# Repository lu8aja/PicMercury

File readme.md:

# PicMercury
This project consists of 4 different boards with PIC18F4550 USB capable microcontrollers
performing several basic I/O actions for the Mercury/Clementina project. The project aims to create
a real size mockup of a Ferranti Mercury valve based computer from the late 1950s.

# Boards
There are 4 boards distributed through the mockup, all communicating through I2C as well as having USB
access to each one, be it for normal access or to use the pieces as standalone.

## Console
The console consists of a keyboard (a 5 x 8 diode matrix with switches and push buttons), an array of 15 leds
(a 4 x 4 diode matrix), a speaker and Plessey connectors to other parts.

The keyboard is logically arranged in 4 10-bits words named Function, Address, Input and Switches

The board controlling the console, acts also as master for I2C communications, allowing a USB connection to
act upon the other boards as well.

## Puncher
The puncher acts as a controller to the punching block "donated" by a Siemens T1000 teleprinter. This punching
block is easily controlled by 7 TTL signals (5 bit punchers, 1 guide puncher and 1 advance solenoid) and
requires 40VDC for all the solenoids.

Additionally, the puncher board has an embedded TTY current loop suitable to control any standard 20mA
teleprinter, like a Siemens T100. Implemented in software it is capable of any arbitrarily low baud rate up
to 110 bauds, level inversions for control and/or data, custom data/stop bit counts.

## Reader
The reader board controls the reader block "donated" by a Siemens T1000 teleprinter, with a stepper motor
and optical paper tape reading.

## Monitor
The original Ferranti Mercury featured a panel with 2 3-inches CRTs and 2 rotating switches that could work
as oscilloscope to serially read values from registers.
The monitor board has proper deflection circuits for driving DG7-32 electrostatic CRTs, with 3 8bits outputs
as R2R DACs. To economize reading the rotary switches, they feature resistors as a voltage divider and an ADC
input of the PIC reads the analog value and obtains the corresponding switch position.
When emulating the Ferranti the console master can write virtual registers and the selector chooses
which register to display.

Additionally and purely for amusement, the USB can directly drive both CRTs, be it for producing something
similar to the dotted Williams Kilburn memories as the Ferranti Mark I used, or other effects. It might be
useful for debug purposes as well. Routines for generating 7 segment numbers are provided.

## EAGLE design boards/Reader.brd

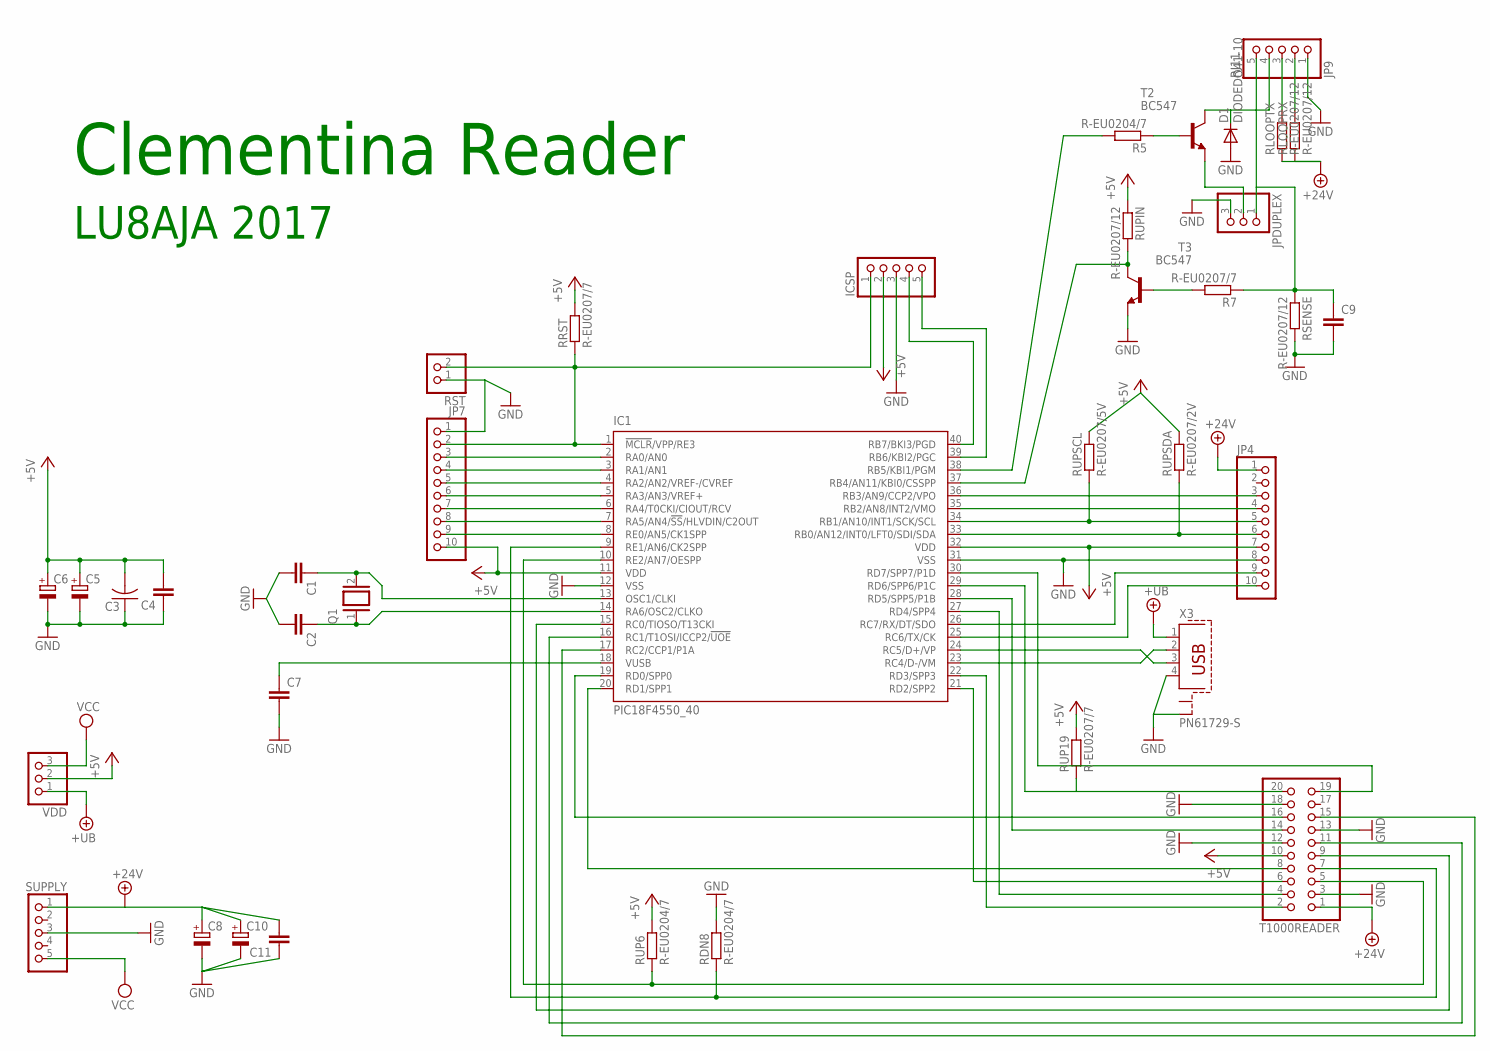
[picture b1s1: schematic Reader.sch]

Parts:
C1, C2: C-EU025-025X050; C025-025X050
C3: C-US025-024X044; C025-024X044
C4, C11: C-EU025-030X050; C025-030X050
C5: CPOL-EUE2.5-6; E2,5-6
C6, C8, C10: CPOL-EUE5-8.5; E5-8,5
C7: C-EU050-025X075; C050-025X075
C9: C-EU050-024X044; C050-024X044
D1: DIODEDO41-10; DO41-10
IC1: PIC18F4550_40; DIL40
ICSP: PINHD-1X5; 1X05
JP4, JP7: PINHD-1X10; 1X10
JP9: RJ11; 1X05
JPDUPLEX: PINHD-1X3; 1X03
Q1: XTAL/S; QS
R5: R-EU0204/7; 0204/7
R7: R-EU0207/7; 0207/7
RDN8: R-EU0204/7; 0204/7
RLOOPRX: R-EU0207/12; 0207/12
RLOOPTX: R-EU0207/12; 0207/12
RRST: R-EU0207/7; 0207/7
RSENSE: R-EU0207/12; 0207/12
RST: PINHD-1X2; 1X02
RUP6: R-EU0204/7; 0204/7
RUP19: R-EU0207/7; 0207/7
RUPIN: R-EU0207/12; 0207/12
RUPSCL: R-EU0207/5V; 0207/5V
RUPSDA: R-EU0207/2V; 0207/2V
SUPPLY: PINHD-1X5; 1X05
T2, T3: BC547; TO92
T1000READER: PINHD-2X10; 2X10
VDD: PINHD-1X3; 1X03
X3: PN61729-S

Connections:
+5V: C3.2, C4.2, C5.+, C6.+, IC1.11 (VDD), IC1.32 (VDD), ICSP.2, JP4.7, JP7.10, RRST.2, RUP6.2, RUP19.2, RUPIN.1, RUPSCL.2, RUPSDA.2, T1000READER.10, VDD.2
+24V: C8.+, C10.+, C11.2, JP4.1, RLOOPRX.1, RLOOPTX.1, SUPPLY.1, T1000READER.1
+UB: VDD.1, X3.1
GND: C1.2, C2.2, C3.1, C4.1, C5.-, C6.-, C7.2, C8.-, C9.2, C10.-, C11.1, D1.A, IC1.12 (VSS), IC1.31 (VSS), ICSP.3, JP4.8, JP7.1, JP9.1, JPDUPLEX.3, RDN8.2, RSENSE.2, RST.1, SUPPLY.3, T3.1 (E), T1000READER.3, T1000READER.12, T1000READER.13, T1000READER.18, X3.4, X3.S2
unnamed: IC1.21 (RD2/SPP2), T1000READER.6
unnamed: C2.1, IC1.14 (RA6/OSC2/CLKO), Q1.1
unnamed: IC1.1 (!MCLR!/VPP/RE3), ICSP.1, JP7.2, RRST.1, RST.2
unnamed: IC1.15 (RC0/TIOSO/T13CKI), T1000READER.9
unnamed: IC1.10 (RE2/AN7/OESPP), RUP6.1, T1000READER.5
unnamed: IC1.9 (RE1/AN6/CK2SPP), RDN8.1, T1000READER.7
unnamed: IC1.8 (RE0/AN5/CK1SPP), JP7.9
unnamed: IC1.7 (RA5/AN4/!SS!/HLVDIN/C2OUT), JP7.8
unnamed: IC1.6 (RA4/T0CKI/CIOUT/RCV), JP7.7
unnamed: C1.1, IC1.13 (OSC1/CLKI), Q1.2
unnamed: IC1.5 (RA3/AN3/VREF+), JP7.6
unnamed: IC1.4 (RA2/AN2/VREF-/CVREF), JP7.5
unnamed: C7.1, IC1.18 (VUSB)
unnamed: JP9.3, RLOOPTX.2
unnamed: JPDUPLEX.2, T2.1 (E)
unnamed: JP9.2, RLOOPRX.2
unnamed: IC1.27 (RD4/SPP4), T1000READER.4
unnamed: IC1.22 (RD3/SPP3), T1000READER.2
unnamed: IC1.17 (RC2/CCP1/P1A), T1000READER.15
unnamed: IC1.16 (RC1/T1OSI/ICCP2/!UOE), T1000READER.11
unnamed: IC1.30 (RD7/SPP7/P1D), T1000READER.19
unnamed: IC1.29 (RD6/SPP6/P1C), RUP19.1, T1000READER.20
unnamed: IC1.28 (RD5/SPP5/P1B), T1000READER.14
unnamed: IC1.24 (RC5/D+/VP), X3.3
unnamed: IC1.3 (RA1/AN1), JP7.4
unnamed: IC1.36 (RB3/AN9/CCP2/VPO), JP4.3
unnamed: IC1.33 (RB0/AN12/INT0/LFT0/SDI/SDA), JP4.6, RUPSDA.1
unnamed: IC1.19 (RD0/SPP0), T1000READER.16
unnamed: IC1.23 (RC4/D-/VM), X3.2
unnamed: IC1.20 (RD1/SPP1), T1000READER.8
unnamed: IC1.25 (RC6/TX/CK), JP4.10
unnamed: IC1.26 (RC7/RX/DT/SDO), JP4.9
unnamed: IC1.34 (RB1/AN10/INT1/SCK/SCL), JP4.5, RUPSCL.1
unnamed: IC1.35 (RB2/AN8/INT2/VMO), JP4.4
unnamed: IC1.2 (RA0/AN0), JP7.3
unnamed: IC1.38 (RB5/KBI1/PGM), R5.2
unnamed: IC1.37 (RB4/AN11/KBI0/CSSPP), RUPIN.2, T3.3 (C)
unnamed: R5.1, T2.2 (B)
unnamed: D1.C, JP9.4, T2.3 (C)
unnamed: IC1.39 (RB6/KBI2/PGC), ICSP.5
unnamed: IC1.40 (RB7/BKI3/PGD), ICSP.4
unnamed: R7.2, T3.2 (B)
unnamed: C9.1, JP9.5, JPDUPLEX.1, R7.1, RSENSE.1
VCC: SUPPLY.5, VDD.3

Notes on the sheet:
LU8AJA 2017
Clementina Reader

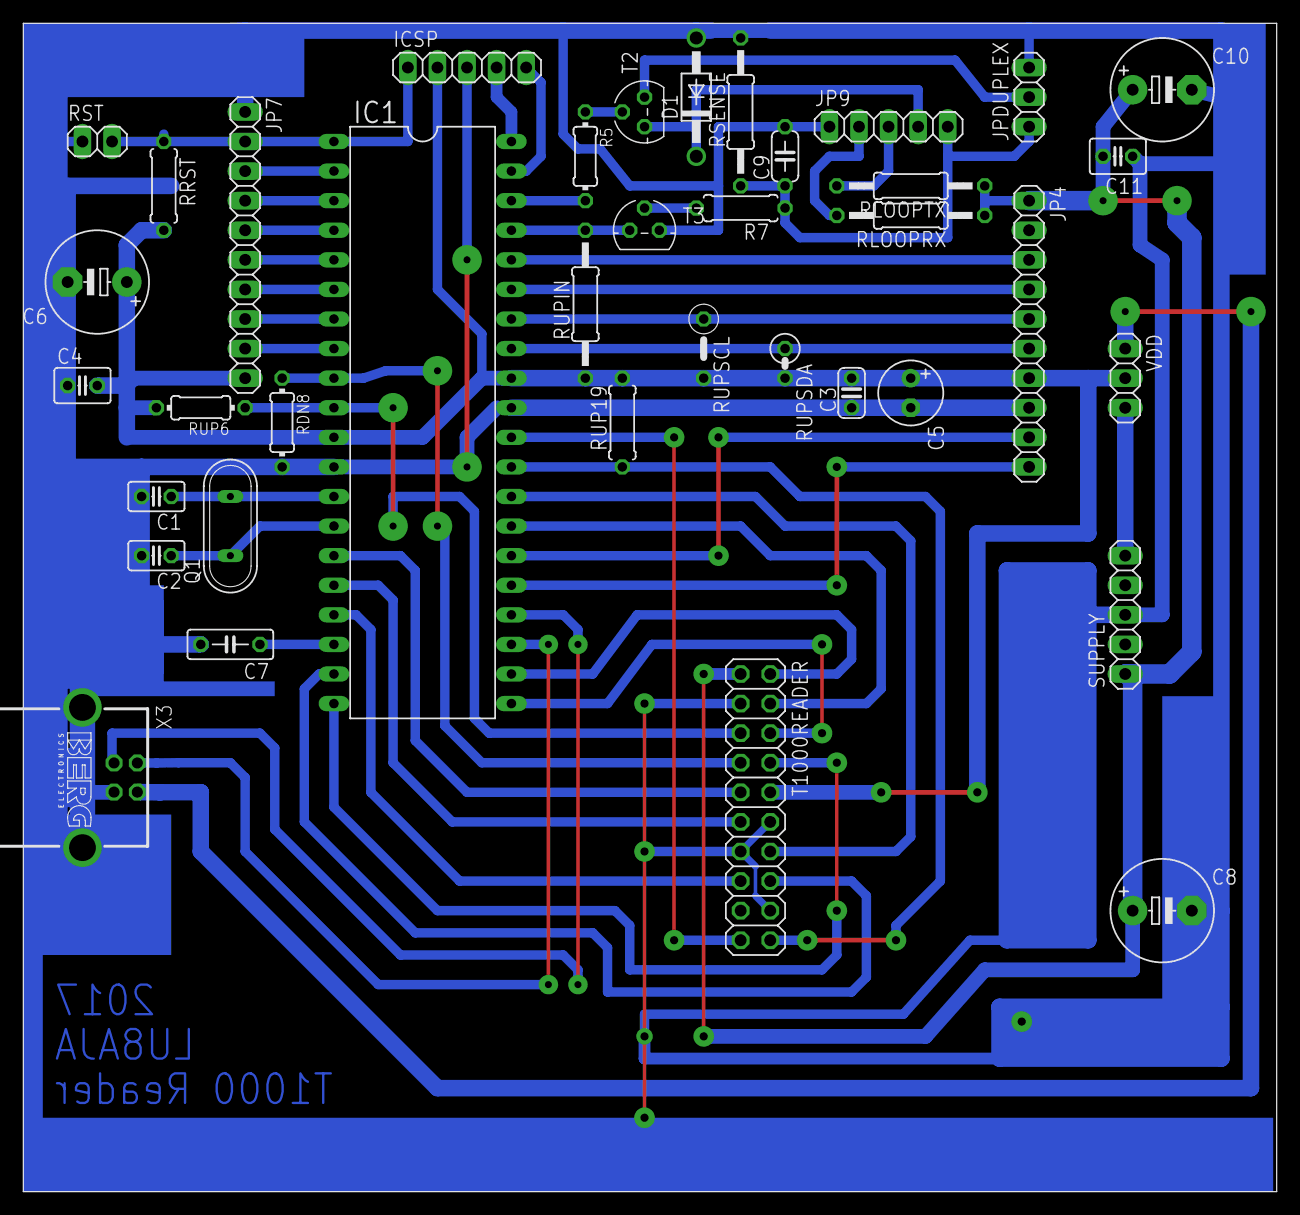
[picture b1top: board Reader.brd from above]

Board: 2 copper layers, 107.6 x 100.3 mm, 38 parts (0 on the bottom side), 48 nets.

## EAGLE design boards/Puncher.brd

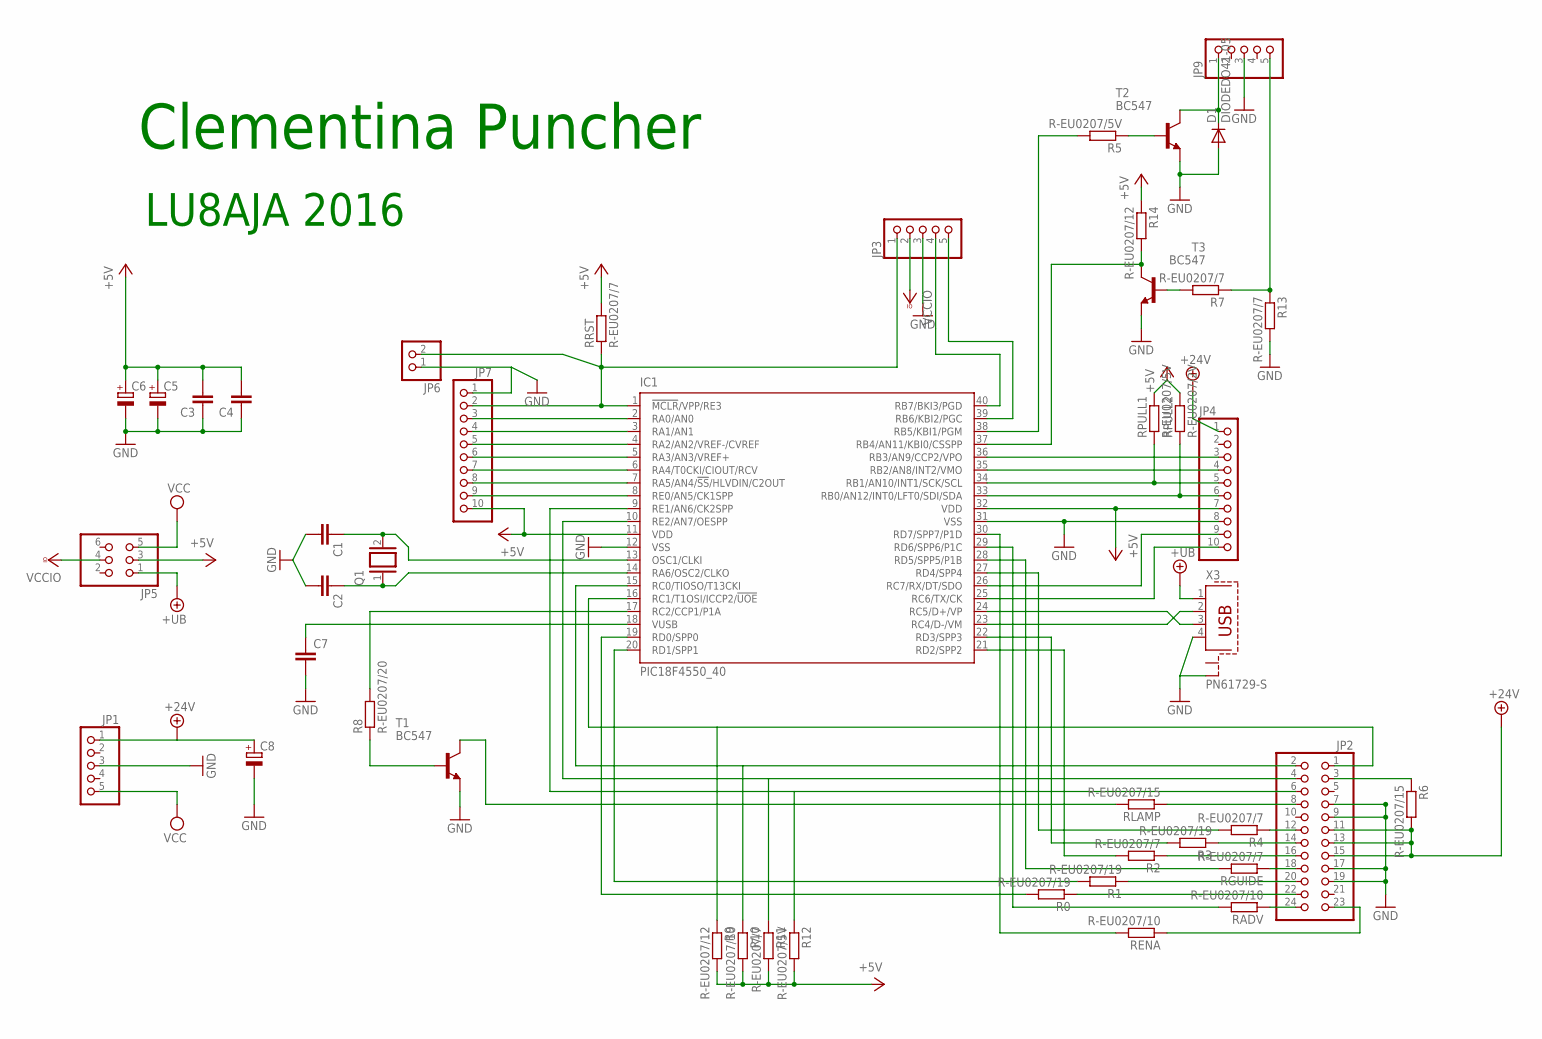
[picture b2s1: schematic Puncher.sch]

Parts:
C1, C2: C-EU025-025X050; C025-025X050
C3, C7: C-EU050-025X075; C050-025X075
C4: C-EU025-030X050; C025-030X050
C5, C6, C8: CPOL-EUE5-8.5; E5-8,5
D1: DIODEDO41-05; DO41-05
IC1: PIC18F4550_40; DIL40
JP1, JP3, JP9: PINHD-1X5; 1X05
JP2: PINHD-2X12; 2X12
JP4, JP7: PINHD-1X10; 1X10
JP5: PINHD-2X3; 2X03
JP6: PINHD-1X2; 1X02
Q1: XTAL/S; QS
R0, R1, R3: R-EU0207/19; 0207/19
R2, R4, R7, R11, R13: R-EU0207/7; 0207/7
R5, R12: R-EU0207/5V; 0207/5V
R6: R-EU0207/15; 0207/15
R8: R-EU0207/20; 0207/20
R9, R14: R-EU0207/12; 0207/12
R10: R-EU0207/10; 0207/10
RADV: R-EU0207/10; 0207/10
RENA: R-EU0207/10; 0207/10
RGUIDE: R-EU0207/7; 0207/7
RLAMP: R-EU0207/15; 0207/15
RPULL1: R-EU0207/5V; 0207/5V
RPULL2: R-EU0207/2V; 0207/2V
RRST: R-EU0207/7; 0207/7
T1, T2, T3: BC547; TO92
X3: PN61729-S

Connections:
+5V: C3.2, C4.2, C5.+, C6.+, IC1.11 (VDD), IC1.32 (VDD), JP4.7, JP5.3, JP7.10, R9.2, R10.2, R11.2, R12.2, R14.1, RPULL1.2, RPULL2.2, RRST.2
+24V: C8.+, JP1.1, JP2.11, JP2.13, JP2.15, JP4.1, R6.2
+UB: JP5.1, X3.1
GND: C1.2, C2.2, C3.1, C4.1, C5.-, C6.-, C7.2, C8.-, D1.A, IC1.12 (VSS), IC1.31 (VSS), JP1.3, JP2.7, JP2.9, JP2.17, JP2.19, JP3.3, JP4.8, JP6.1, JP7.1, JP9.3, R13.2, T1.1 (E), T2.1 (E), T3.1 (E), X3.4, X3.S2
unnamed: JP2.24, RADV.1
unnamed: C2.1, IC1.14 (RA6/OSC2/CLKO), Q1.1
unnamed: IC1.1 (!MCLR!/VPP/RE3), JP3.1, JP6.2, JP7.2, RRST.1
unnamed: IC1.17 (RC2/CCP1/P1A), R8.2
unnamed: IC1.16 (RC1/T1OSI/ICCP2/!UOE), JP2.1, R9.1
unnamed: IC1.15 (RC0/TIOSO/T13CKI), JP2.2, R10.1
unnamed: IC1.10 (RE2/AN7/OESPP), JP2.4, R11.1
unnamed: IC1.9 (RE1/AN6/CK2SPP), JP2.6, R12.1
unnamed: IC1.8 (RE0/AN5/CK1SPP), JP7.9
unnamed: IC1.7 (RA5/AN4/!SS!/HLVDIN/C2OUT), JP7.8
unnamed: IC1.6 (RA4/T0CKI/CIOUT/RCV), JP7.7
unnamed: C1.1, IC1.13 (OSC1/CLKI), Q1.2
unnamed: IC1.5 (RA3/AN3/VREF+), JP7.6
unnamed: IC1.4 (RA2/AN2/VREF-/CVREF), JP7.5
unnamed: C7.1, IC1.18 (VUSB)
unnamed: JP2.22, R0.1
unnamed: IC1.22 (RD3/SPP3), R3.2
unnamed: JP2.20, R1.1
unnamed: JP2.18, RGUIDE.1
unnamed: JP2.16, R2.1
unnamed: JP2.14, R3.1
unnamed: JP2.12, R4.1
unnamed: JP2.23, RENA.1
unnamed: IC1.30 (RD7/SPP7/P1D), RENA.2
unnamed: IC1.29 (RD6/SPP6/P1C), RADV.2
unnamed: IC1.28 (RD5/SPP5/P1B), RGUIDE.2
unnamed: IC1.24 (RC5/D+/VP), X3.3
unnamed: IC1.3 (RA1/AN1), JP7.4
unnamed: IC1.36 (RB3/AN9/CCP2/VPO), JP4.3
unnamed: IC1.33 (RB0/AN12/INT0/LFT0/SDI/SDA), JP4.6, RPULL2.1
unnamed: IC1.27 (RD4/SPP4), R4.2
unnamed: IC1.21 (RD2/SPP2), R2.2
unnamed: IC1.23 (RC4/D-/VM), X3.2
unnamed: IC1.20 (RD1/SPP1), R1.2
unnamed: IC1.19 (RD0/SPP0), R0.2
unnamed: IC1.25 (RC6/TX/CK), JP4.10
unnamed: IC1.26 (RC7/RX/DT/SDO), JP4.9
unnamed: IC1.34 (RB1/AN10/INT1/SCK/SCL), JP4.5, RPULL1.1
unnamed: IC1.35 (RB2/AN8/INT2/VMO), JP4.4
unnamed: JP2.8, RLAMP.1
unnamed: JP2.3, R6.1
unnamed: RLAMP.2, T1.3 (C)
unnamed: R8.1, T1.2 (B)
unnamed: IC1.2 (RA0/AN0), JP7.3
unnamed: IC1.38 (RB5/KBI1/PGM), R5.2
unnamed: IC1.37 (RB4/AN11/KBI0/CSSPP), R14.2, T3.3 (C)
unnamed: R5.1, T2.2 (B)
unnamed: D1.C, JP9.1, T2.3 (C)
unnamed: IC1.39 (RB6/KBI2/PGC), JP3.5
unnamed: IC1.40 (RB7/BKI3/PGD), JP3.4
unnamed: R7.2, T3.2 (B)
unnamed: JP9.5, R7.1, R13.1
VCC: JP1.5, JP5.5
VCCIO: JP3.2, JP5.4

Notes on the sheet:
LU8AJA 2016
Clementina Puncher

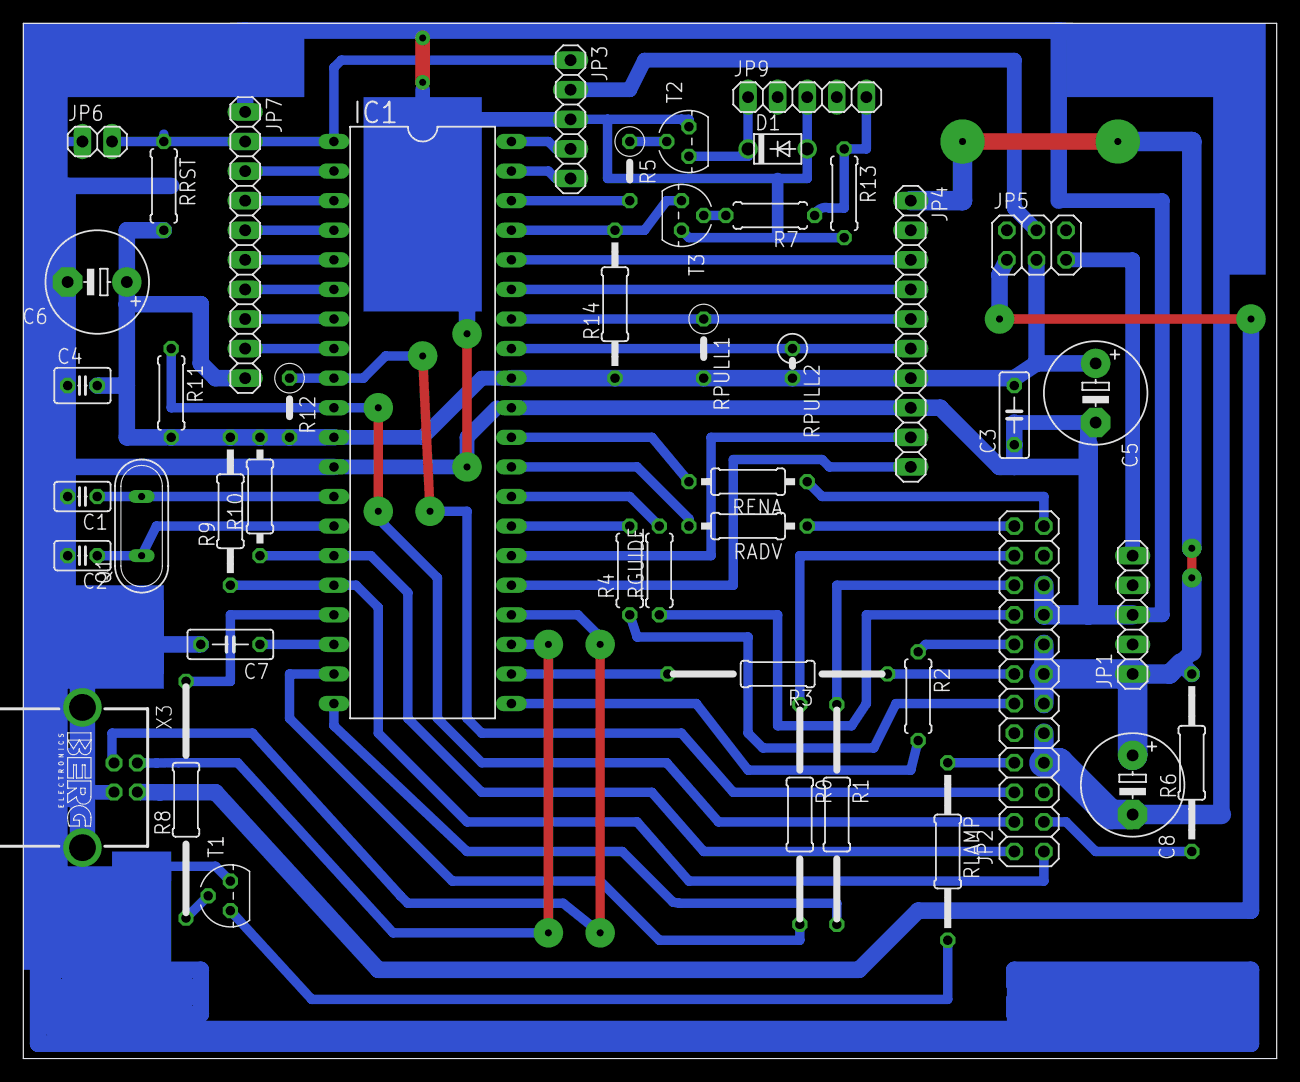
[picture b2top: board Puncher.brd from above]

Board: 2 copper layers, 107.6 x 88.9 mm, 45 parts (0 on the bottom side), 58 nets.

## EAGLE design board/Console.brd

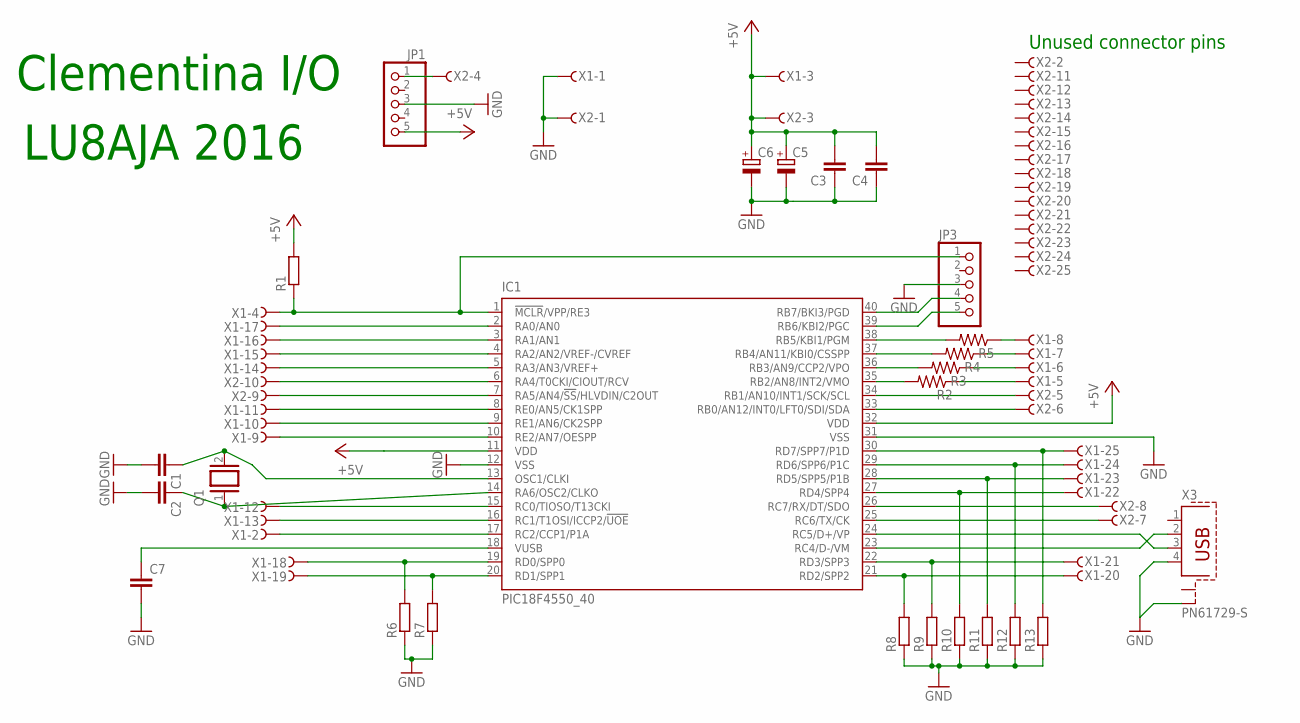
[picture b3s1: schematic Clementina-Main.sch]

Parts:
C1, C2: C-EU025-025X050; C025-025X050
C3, C7: C-EU050-025X075; C050-025X075
C4: C-EU050-030X075; C050-030X075
C5, C6: CPOL-EUE5-8.5; E5-8,5
IC1: PIC18F4550_40; DIL40
JP1, JP3: PINHD-1X5; 1X05
Q1: XTAL/S; QS
R1, R6, R7, R8, R9, R10, R11, R12, R13: R-EU_0207/15; 0207/15
R2, R3, R4, R5: R-US_0207/15; 0207/15
X1, X2: F25HPS; F25HP
X3: PN61729-S

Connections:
+5V: C3.2, C4.2, C5.+, C6.+, IC1.11 (VDD), IC1.32 (VDD), JP1.5, R1.2, X1.3 (F), X2.3 (F)
GND: C1.2, C2.2, C3.1, C4.1, C5.-, C6.-, C7.2, IC1.12 (VSS), IC1.31 (VSS), JP1.3, JP3.3, R6.1, R7.1, R8.1, R9.1, R10.1, R11.1, R12.1, R13.1, X1.1 (F), X2.1 (F), X3.4, X3.S2
unnamed: IC1.19 (RD0/SPP0), R6.2, X1.18 (F)
unnamed: C2.1, IC1.14 (RA6/OSC2/CLKO), Q1.1
unnamed: IC1.1 (!MCLR!/VPP/RE3), JP3.1, R1.1, X1.4 (F)
unnamed: IC1.8 (RE0/AN5/CK1SPP), X1.11 (F)
unnamed: IC1.9 (RE1/AN6/CK2SPP), X1.10 (F)
unnamed: IC1.10 (RE2/AN7/OESPP), X1.9 (F)
unnamed: IC1.2 (RA0/AN0), X1.17 (F)
unnamed: IC1.3 (RA1/AN1), X1.16 (F)
unnamed: IC1.4 (RA2/AN2/VREF-/CVREF), X1.15 (F)
unnamed: IC1.5 (RA3/AN3/VREF+), X1.14 (F)
unnamed: IC1.15 (RC0/TIOSO/T13CKI), X1.12 (F)
unnamed: C1.1, IC1.13 (OSC1/CLKI), Q1.2
unnamed: IC1.16 (RC1/T1OSI/ICCP2/!UOE), X1.13 (F)
unnamed: IC1.17 (RC2/CCP1/P1A), X1.2 (F)
unnamed: C7.1, IC1.18 (VUSB)
unnamed: IC1.20 (RD1/SPP1), R7.2, X1.19 (F)
unnamed: IC1.21 (RD2/SPP2), R8.2, X1.20 (F)
unnamed: IC1.22 (RD3/SPP3), R9.2, X1.21 (F)
unnamed: IC1.27 (RD4/SPP4), R10.2, X1.22 (F)
unnamed: IC1.28 (RD5/SPP5/P1B), R11.2, X1.23 (F)
unnamed: IC1.29 (RD6/SPP6/P1C), R12.2, X1.24 (F)
unnamed: IC1.30 (RD7/SPP7/P1D), R13.2, X1.25 (F)
unnamed: IC1.35 (RB2/AN8/INT2/VMO), R2.2
unnamed: IC1.36 (RB3/AN9/CCP2/VPO), R3.2
unnamed: IC1.37 (RB4/AN11/KBI0/CSSPP), R4.2
unnamed: IC1.38 (RB5/KBI1/PGM), R5.2
unnamed: IC1.24 (RC5/D+/VP), X3.3
unnamed: IC1.6 (RA4/T0CKI/CIOUT/RCV), X2.10 (F)
unnamed: IC1.7 (RA5/AN4/!SS!/HLVDIN/C2OUT), X2.9 (F)
unnamed: IC1.34 (RB1/AN10/INT1/SCK/SCL), X2.5 (F)
unnamed: IC1.33 (RB0/AN12/INT0/LFT0/SDI/SDA), X2.6 (F)
unnamed: IC1.26 (RC7/RX/DT/SDO), X2.8 (F)
unnamed: IC1.25 (RC6/TX/CK), X2.7 (F)
unnamed: IC1.23 (RC4/D-/VM), X3.2
unnamed: JP1.1, X2.4 (F)
unnamed: R5.1, X1.8 (F)
unnamed: R4.1, X1.7 (F)
unnamed: R3.1, X1.6 (F)
unnamed: R2.1, X1.5 (F)
unnamed: IC1.39 (RB6/KBI2/PGC), JP3.5
unnamed: IC1.40 (RB7/BKI3/PGD), JP3.4

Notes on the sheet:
LU8AJA 2016
Clementina I/O
Unused connector pins

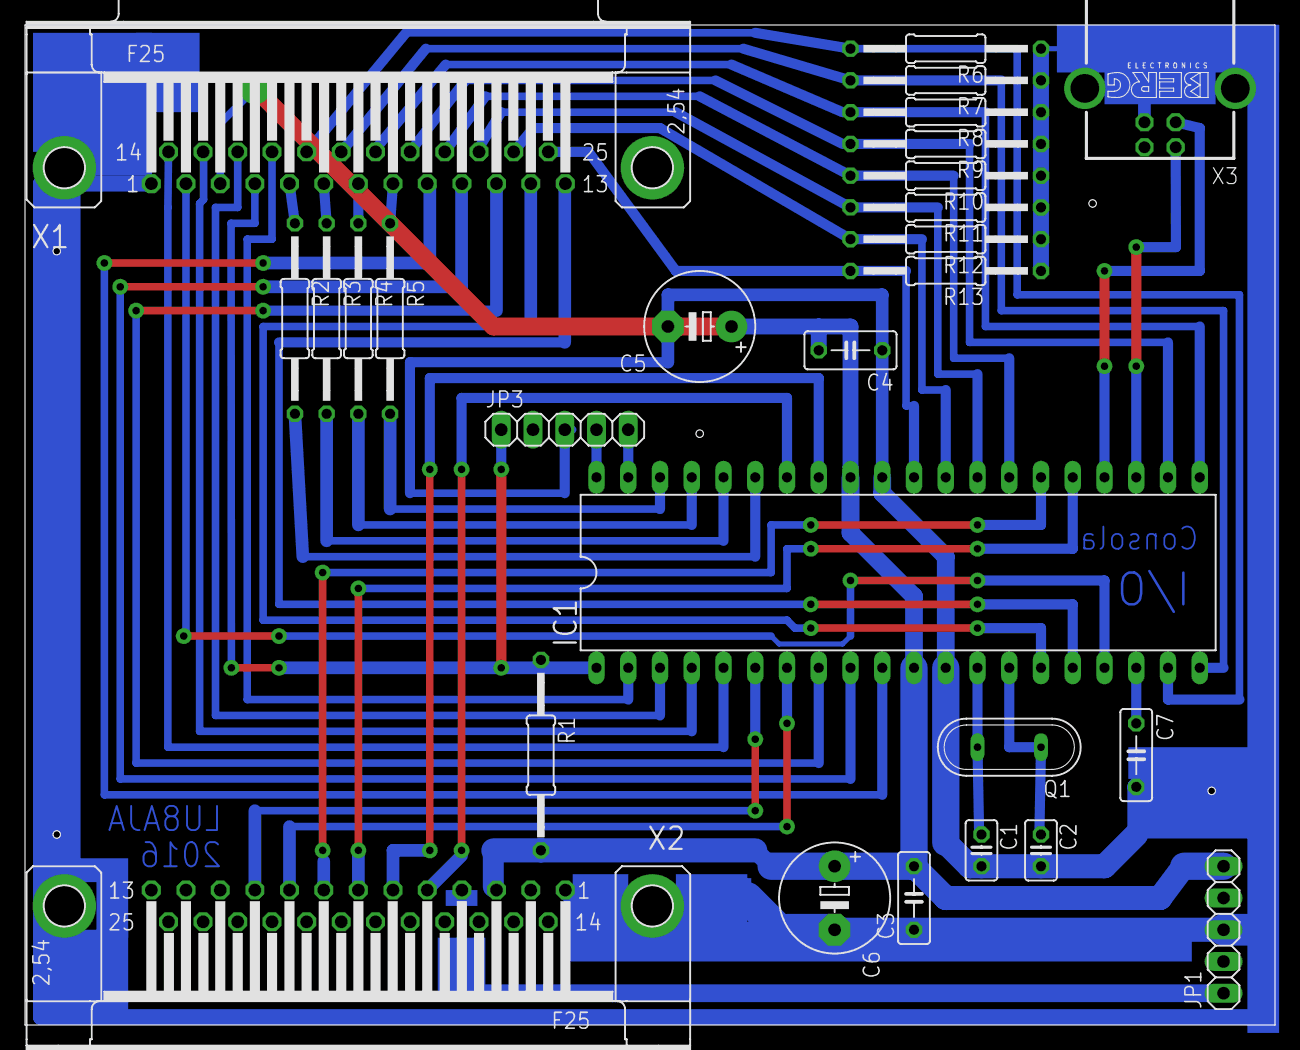
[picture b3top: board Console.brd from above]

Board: 2 copper layers, 100.0 x 80.0 mm, 27 parts (0 on the bottom side), 43 nets.

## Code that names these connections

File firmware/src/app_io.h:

/* 
 * File:   app_io.h
 * Author: Javier
 *
 * Created on February 21, 2017, 8:11 PM
 */

// 

#define CFG_BOARD_XTAL_FREQ 20000000

/*** KEYS Related ***/
    #define PIN_HOOT_OUT  LATCbits.LATC2
    #define PIN_HOOT_TRIS TRISCbits.RC2

    #define PIN_KEYS_OUT_0 LATEbits.LATE0 
    #define PIN_KEYS_OUT_1 LATEbits.LATE1 
    #define PIN_KEYS_OUT_2 LATEbits.LATE2 
    #define PIN_KEYS_OUT_3 LATCbits.LATC0 
    #define PIN_KEYS_OUT_4 LATCbits.LATC1

    #define PIN_KEYS_OUT_0_TRIS TRISEbits.RE0 
    #define PIN_KEYS_OUT_1_TRIS TRISEbits.RE1 
    #define PIN_KEYS_OUT_2_TRIS TRISEbits.RE2 
    #define PIN_KEYS_OUT_3_TRIS TRISCbits.RC0 
    #define PIN_KEYS_OUT_4_TRIS TRISCbits.RC1

    #define PIN_KEYS_IN      PORTD
    #define PIN_KEYS_IN_TRIS TRISD


    typedef struct {
            unsigned char out_port;
            unsigned char out_bit;
            unsigned char in_port;
            unsigned char in_bit;
    } button_map_t;

    #define MasterButtonsMapLen 3
    extern button_map_t MasterButtonsMap[];

    #define MasterButtonsHistoryBits 7
    typedef struct {
            unsigned char status:1;
            unsigned char history:7;
    } button_status_t;

    #define MasterButtonsLen 3
    extern button_status_t MasterButtons[];


/*** LED Related ***/
    #define LEDS_ANODES          0b00111100
    #define LEDS_ANODES_SHIFT    2
    #define LEDS_ANODES_TRIS     TRISB
    #define LEDS_ANODES_LAT      LATB

    #define LEDS_CATHODES        0b00001111
    #define LEDS_CATHODES_SHIFT  0
    #define LEDS_CATHODES_TRIS   TRISA
    #define LEDS_CATHODES_LAT    LATA

    #define LED_USB    0x0f
    #define LED_ALARM  0x00

    
    /*
    #define MasterLedMapLen 16
    extern const unsigned char MasterLedMap[];
    */

/*** I2C Related ***/
    #define CFG_I2C_ADDRESS_MASTER  0x01       // NEVER change this one, it is used internally by slaves to notify master, nothing to do with actual I2C addresses!
    #define CFG_I2C_ADDRESS_CONSOLE 0b00010000 // Not actually used over the wire because it is master
    #define CFG_I2C_ADDRESS_PUNCHER 0b00100000
    #define CFG_I2C_ADDRESS_READER  0b01000000
    #define CFG_I2C_ADDRESS_MONITOR    0b10000000

/*** SoftSerial Related ***/
    #define CFG_SOFTSERIAL_TX_Port        'B'
    #define CFG_SOFTSERIAL_TX_Pin          5
    #define CFG_SOFTSERIAL_TX_InvertCtrl   1
    #define CFG_SOFTSERIAL_TX_InvertData   0
    #define CFG_SOFTSERIAL_RX_Port        'B'
    #define CFG_SOFTSERIAL_RX_Pin          4
    #define CFG_SOFTSERIAL_RX_InvertCtrl   1
    #define CFG_SOFTSERIAL_RX_InvertData   1
    #define CFG_SOFTSERIAL_RX_DataBits     5
    #define CFG_SOFTSERIAL_RX_StopBits     1
    #define CFG_SOFTSERIAL_RX_Period       20
    #define CFG_SOFTSERIAL_HalfDuplex      1
    #define CFG_SOFTSERIAL_Transcode       3

    #define CFG_TRANSCODER_CODE            1

/*** Misc ***/

#define INPUT   1
#define OUTPUT  0

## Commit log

2017-02-14 Initial Commit based upon PicDemFS
2017-02-19 v0.1 Initial working based upon CDC example
2017-02-21 Leds & Tones added
2017-02-22 Cleanup and split into app_* files. Midi added. High interrupt made more efficient.
2017-02-23 CMD simplification. Reply management changes. Read/Write commands entirely rewrote. Added button debounce logic.
2017-02-23 New Cmds: keys, run, var. New PseudoCmds: wait, uart. Bugfix to int2binstr and associated led renumbering. Lots of rewrite to output buffer handling.
2017-03-02 Moved to a more modular structure with service files. Added board profiles.
2017-03-02 Changed line ending style to Win for MPLAB compatibility
2017-03-02 Cmd Execute now receives buffers. I2C works.
2017-03-02 Project renamed in MPLAB
2017-03-04 Misc Tweaks
2017-03-04 Added Docs & Boards
2017-03-06 Minor fixes and tweaks
2017-03-10 New SoftSerial service added
2017-03-10 SoftSerial: Reimplemented using ring buffers and heap
2017-03-18 New Transcoder library, used by SoftSerial and Puncher. MasterClock into a struct. Small changes across the board.
2017-03-20 APP USB into its own service. Updated CMDs to pass reply buffer.
2017-03-24 I2C: Heavily reworked with a basic size + idBuffer protocol
2017-03-24 SoftSerial: Implemented different invert flags for data and control
2017-03-24 Commands: Change the way commands are checked, across the board
2017-03-25 Buttons: Change implementation to use chars instead of pointers
2017-03-25 Programs: Added custom example programs
2017-03-25 Docs: Updated wiring
2017-04-01 Serial: Implemented commands
2017-04-01 Puncher: Split cfg cmd
2017-04-07 I2C: Enhanced protocol to allow from/to addresses with ports. Serial/Punch: Now support escaped sequences. Cmds: Implemented idBuffer as replacement of pBuffers. Readme added.
2017-04-08 SoftSerial: Added EEPROM configs. Ring: Enhanced escaping sequences. Docs: updated MDs.
2017-04-08 Transcoder: AutoCrLf and Column tracking
2017-04-15 Reader: Added new service
2017-04-21 Reader: General service rework with new logic
